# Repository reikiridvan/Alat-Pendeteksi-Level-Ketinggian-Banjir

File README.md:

Pendeteksi level ketinggian banjir merupakan suatu perangkat yang nantinya digunakan untuk mengukur tingkat level bencana pada sebuah banjir. Dengan menggunakan rangkaian mikrokontroler AVR, output yang di keluarkan akan berformat MP4 dan output suara akan berbeda tergantung tiap tinggi rendahnya level bencana.

`WORKSHOP MIKROKONTROLLER - PROGRAM STUDI TEKNIK ELEKTRONIKA - POLITEKNIK ELEKTRONIKA NEGERI SURABAYA`

`DOSEN PENGAMPU : Akhmad Hendriawan ST, MT`
`NIP. 197501272002121003`

`TEAM`
| No.  | Nama  | NRP  | Pembagian Tugas  |
| :------------: | :------------: | :------------: | :------------: |
| 1  | Moch.Rizky Faturrohman  | 2122500003  | 3D design |
| 2  | Dimas Ramadhani | 2122500004  | Dokumentasi proyek dan pembuatan cover  |
| 3  |  Reiki Ridvan | 2122500015  |  Perancangan Program Untuk Arduino UNO |
| 4  |  Ahmad Rayhan Adhitama  |  2122500017 |  Melakukan proses soldering Komponen pada PCB |
| 5  |  Moch Reyhan Yudha Saputra | 2122500023  |  Publikasi Rancangan Alat Melalui Github, Desain Skematik dan Board PCB |
| 6  | Dwi Satrio Nugroho  |  2122500024 | Desain Skematik dan Board PCB, Proses soldering Komponen pada PCB |

## Daftar Isi
- [Komponen Yang Digunakan](#Komponen-Yang-Digunakan)
- [Blok Diagram](#Blok-Diagram)
- [Fitur](#Fitur)
- [Desain Rangkaian](#Desain-Rangkaian)
- [3D Design](#3D-Design)
- [PCB](#PCB)
- [Dokumentasi Proyek](#Dokumentasi-Proyek)

## Komponen Yang Digunakan
1. Arduino UNO R3
2. Water level sensor
3. Push Button
4. Speaker
5. Amplifier PAM8403 DC 5V

## Blok Diagram

Pada alat pendeteksi banjir yang telah kita buat, memiliki prinsip kerja yiatu dimana kita disini menggunakna Arduino UNO sebagai mikrokontroler yang digunakan yang dimana akan disupply teganggan berupa battery. Pertama Water level sensor akan mulai membaca nilai, jika nilai yang dibaca pada Water level sensor bernilai lebih dari "1000" maka Speaker akan mulai mengeluarkan suara yang sudah di inputkan di arduino, output suara yang dihasilkan kurang lebih seperti alarm "Awas Ada Banjir" yang akan di suarakan melalui speaker yang telah dikuatkan menggunakna Amplifier 5V. Jika dirasa durasi Alarm terlalu lama sehingga membuat warga sekitar panik, maka alarm dapat dimatikan menggunakan push button yang berfungsi sebagai interrupt untuk menghentikan pembacaan Water level sensor
   
## Fitur
- Pembangkitan sinyal audio mikrokontroler AVR
- Push Button sebagai interuppt alarm audio
- Output audio sebagai alarm

## Desain Rangkaian
Berikut adalah skematik breadbord untuk simulasi menggunakan Wokwi yang menggunakan Arduino Uno

## 3D Design
Berikut adalah hasil 3D Design menggunakan TinkerCad :

1. 3D Design konsep alat

2. 3D Design Package

3. Hasil cetak case arduino

Berikut adalah tutorial dalam pembuatan desain case Arduino UNO menggunakan Thinkercad pada proyek ini. Bisa klik link [berikut.](https://youtu.be/i5TSe1QAH68?si=4G1KmNbXgsI5xHIV "berikut.")

https://github.com/reikiridvan/Alat-Pendeteksi-Level-Ketinggian-Banjir/assets/168399517/43fbf41c-e08d-4e37-8248-c662943a5e90

## PCB
Berikut Program Design PCB yang telah dibuat :

1. Schematic

2. Board

3. Design 3D

4. Hasil Cetak PCB

Video Tutorial :Langkah - langkah pembuatan PCB

https://github.com/reikiridvan/Alat-Pendeteksi-Level-Ketinggian-Banjir/assets/134507164/7d09def3-0b46-4763-8496-2ca6ddae62d7

## Audio Project
Berikut hasil pembuatan audio dengan hasil editnya menggunakan software Audacity yang kemudian didapatkan file raw yang dibuka melalui software HxD untuk memperoleh datanya dan didapatkan program bahasa C. Program bahasa C tersebut digunakan untuk memrogram Arduino UNO agar audio berfungsi. Berikut hasil dokumentasinya :

Video Tutorial : Langkah - Langkah Convert Audio Ke Bahasa C

   https://github.com/reikiridvan/Alat-Pendeteksi-Level-Ketinggian-Banjir/assets/134507164/44a9ac11-2886-480d-8157-06fb5abc79b8

## Dokumentasi Proyek
1. Pembuatan program dan simulasi rangkaian

2. Pengetesan Water level sensor

3. Pengetesan Speaker

   https://github.com/reikiridvan/Alat-Pendeteksi-Level-Ketinggian-Banjir/assets/168399517/ead18a85-f2a6-42ef-aa6f-99f8f66ff1ce

4. Pengetesan Water Level

   https://github.com/reikiridvan/Alat-Pendeteksi-Level-Ketinggian-Banjir/assets/168399517/9324a78c-4d6f-4962-8cf6-fae1af6c441c

5. Pengetesan Alat
   
   https://github.com/reikiridvan/Alat-Pendeteksi-Level-Ketinggian-Banjir/assets/168399517/c71d29dc-50ec-499a-8ccf-71fea559822b

6. Video Promosi
   
   Untuk Video promosi dari "alat pendeteksi ketinggian banjir" yang telah dibuat dapat dilihat pada link [berikut.](https://youtu.be/Jxg5Ch7Bdpk "berikut.")

7. Video Presentasi

   Video presentasi, penjelasan dari "alat pendeteksi ketinggian banjir" dapat dilihat pada link [berikut.](https://www.youtu.be/Jxg5Ch7Bdpk&t "berikut.")

9. poster

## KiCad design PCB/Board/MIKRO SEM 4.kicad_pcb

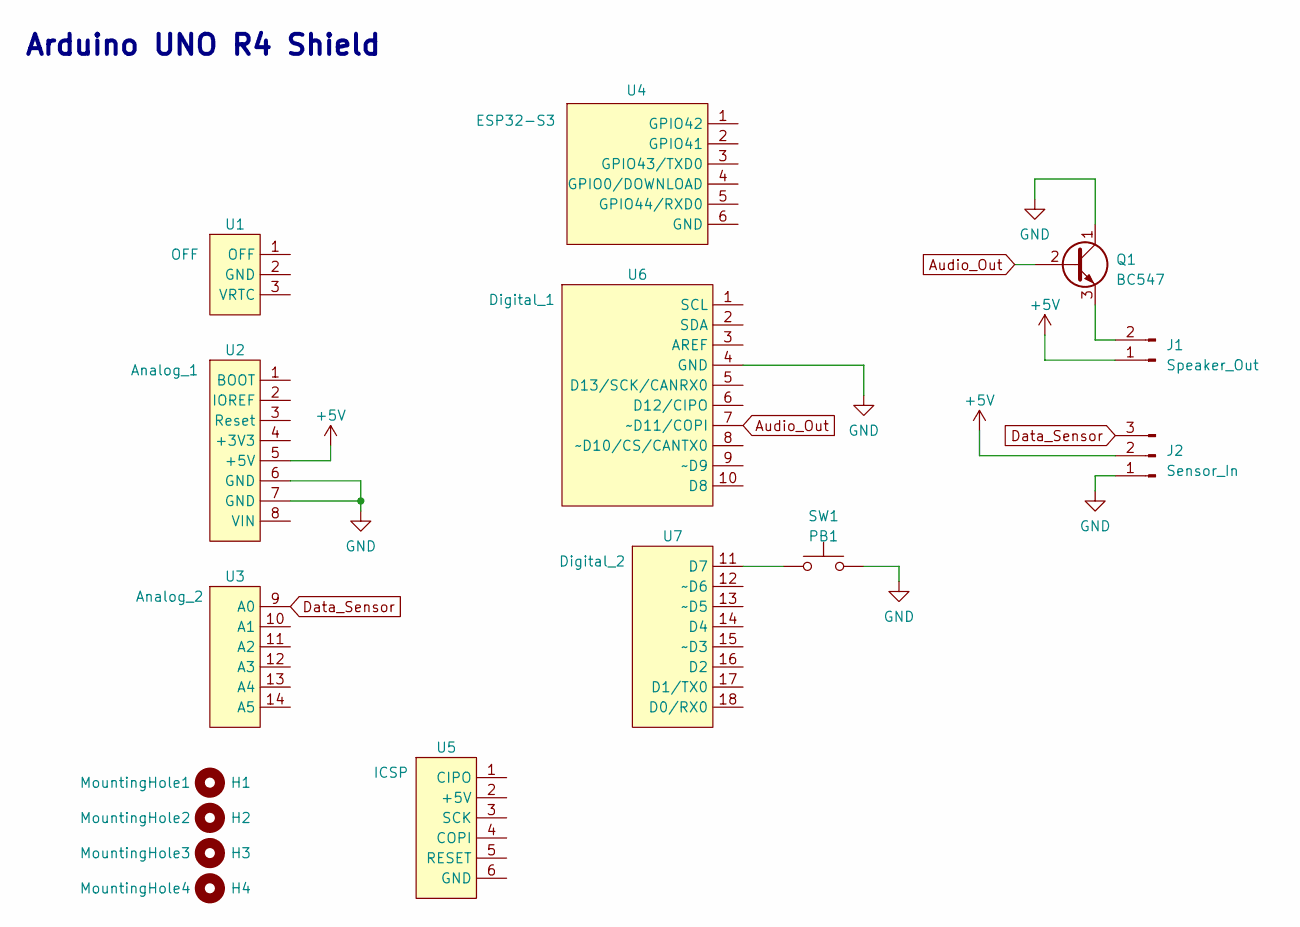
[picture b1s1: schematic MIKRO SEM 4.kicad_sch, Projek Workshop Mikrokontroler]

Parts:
H1: MountingHole1; Arduino_MountingHole
H2: MountingHole2; Arduino_MountingHole
H3: MountingHole3; Arduino_MountingHole
H4: MountingHole4; Arduino_MountingHole
J1: Speaker_Out; PinHeader_1x02_P2.54mm_Vertical
J2: Sensor_In; PinHeader_1x03_P2.54mm_Vertical
Q1: BC547; TO-92_Inline_Wide
SW1: PB1; SW_PUSH_6mm
U1: OFF; Arduino_PinSocket_1x03_P2.54mm_Vertical
U2: Analog_1; Arduino_PinSocket_1x08_P2.54mm_Vertical
U3: Analog_2; Arduino_PinSocket_1x06_P2.54mm_Vertical
U4: ESP32-S3; Arduino_PinSocket_2x03_P2.54mm_Vertical
U5: ICSP; Arduino_PinSocket_2x03_P2.54mm_Vertical
U6: Digital_1; Arduino_PinSocket_1x10_P2.54mm_Vertical
U7: Digital_2; Arduino_PinSocket_1x08_P2.54mm_Vertical

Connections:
+5V: J1.1, J2.2, U2.5 (+5V)
Audio_Out: Q1.2 (B), U6.7 (~D11/COPI)
Data_Sensor: J2.3, U3.9 (A0)
GND: J2.1, Q1.1 (C), SW1.2, U2.6 (GND), U2.7 (GND), U6.4 (GND)
unnamed: J1.2, Q1.3 (E)
unnamed: SW1.1, U7.11 (D7)

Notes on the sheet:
Arduino UNO R4 Shield

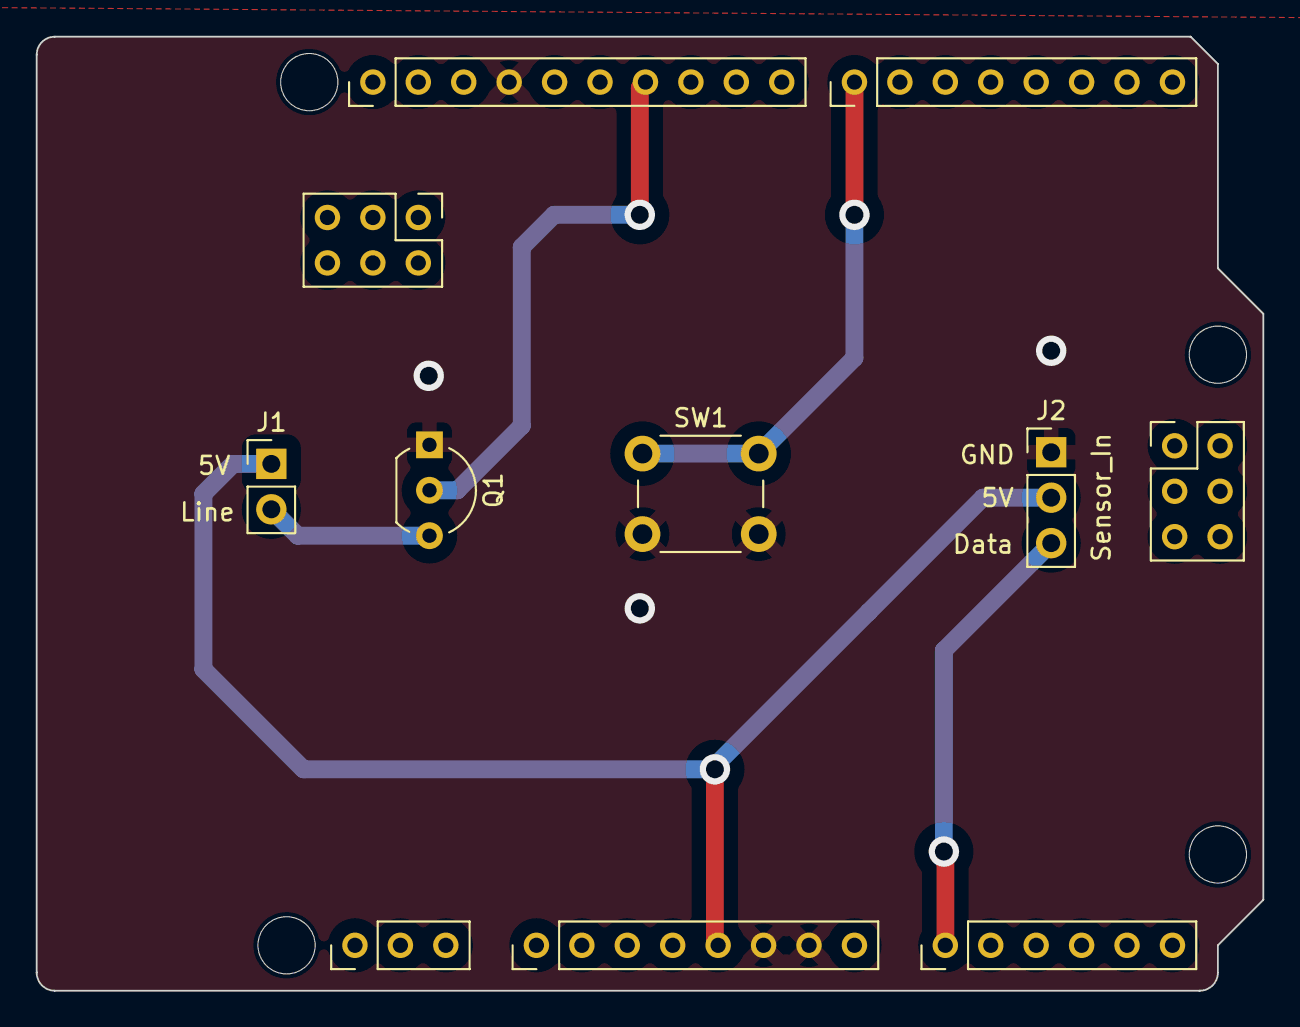
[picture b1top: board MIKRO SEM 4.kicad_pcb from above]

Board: 2 copper layers, 68.6 x 53.3 mm, 15 parts (0 on the bottom side), 6 nets.

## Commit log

2024-05-06 Skech 05 05 2024
2024-05-06 Rename WhatsApp Image 2024-05-06 at 09.53.12_5e5bec69.jpg to Desain Rangkaian
2024-05-13 Create Test
2024-05-13 Desain 3d
2024-05-13 Create Dokumentasi
2024-05-19 Create DATA SHEET
2024-05-19 DATA SHEET
2024-05-20 Desain Rangkaian
2024-05-20 Test Code
2024-05-20 3D Design
2024-05-26 Dokumentasi Proyek
2024-05-27 Audio
2024-06-02 Program
